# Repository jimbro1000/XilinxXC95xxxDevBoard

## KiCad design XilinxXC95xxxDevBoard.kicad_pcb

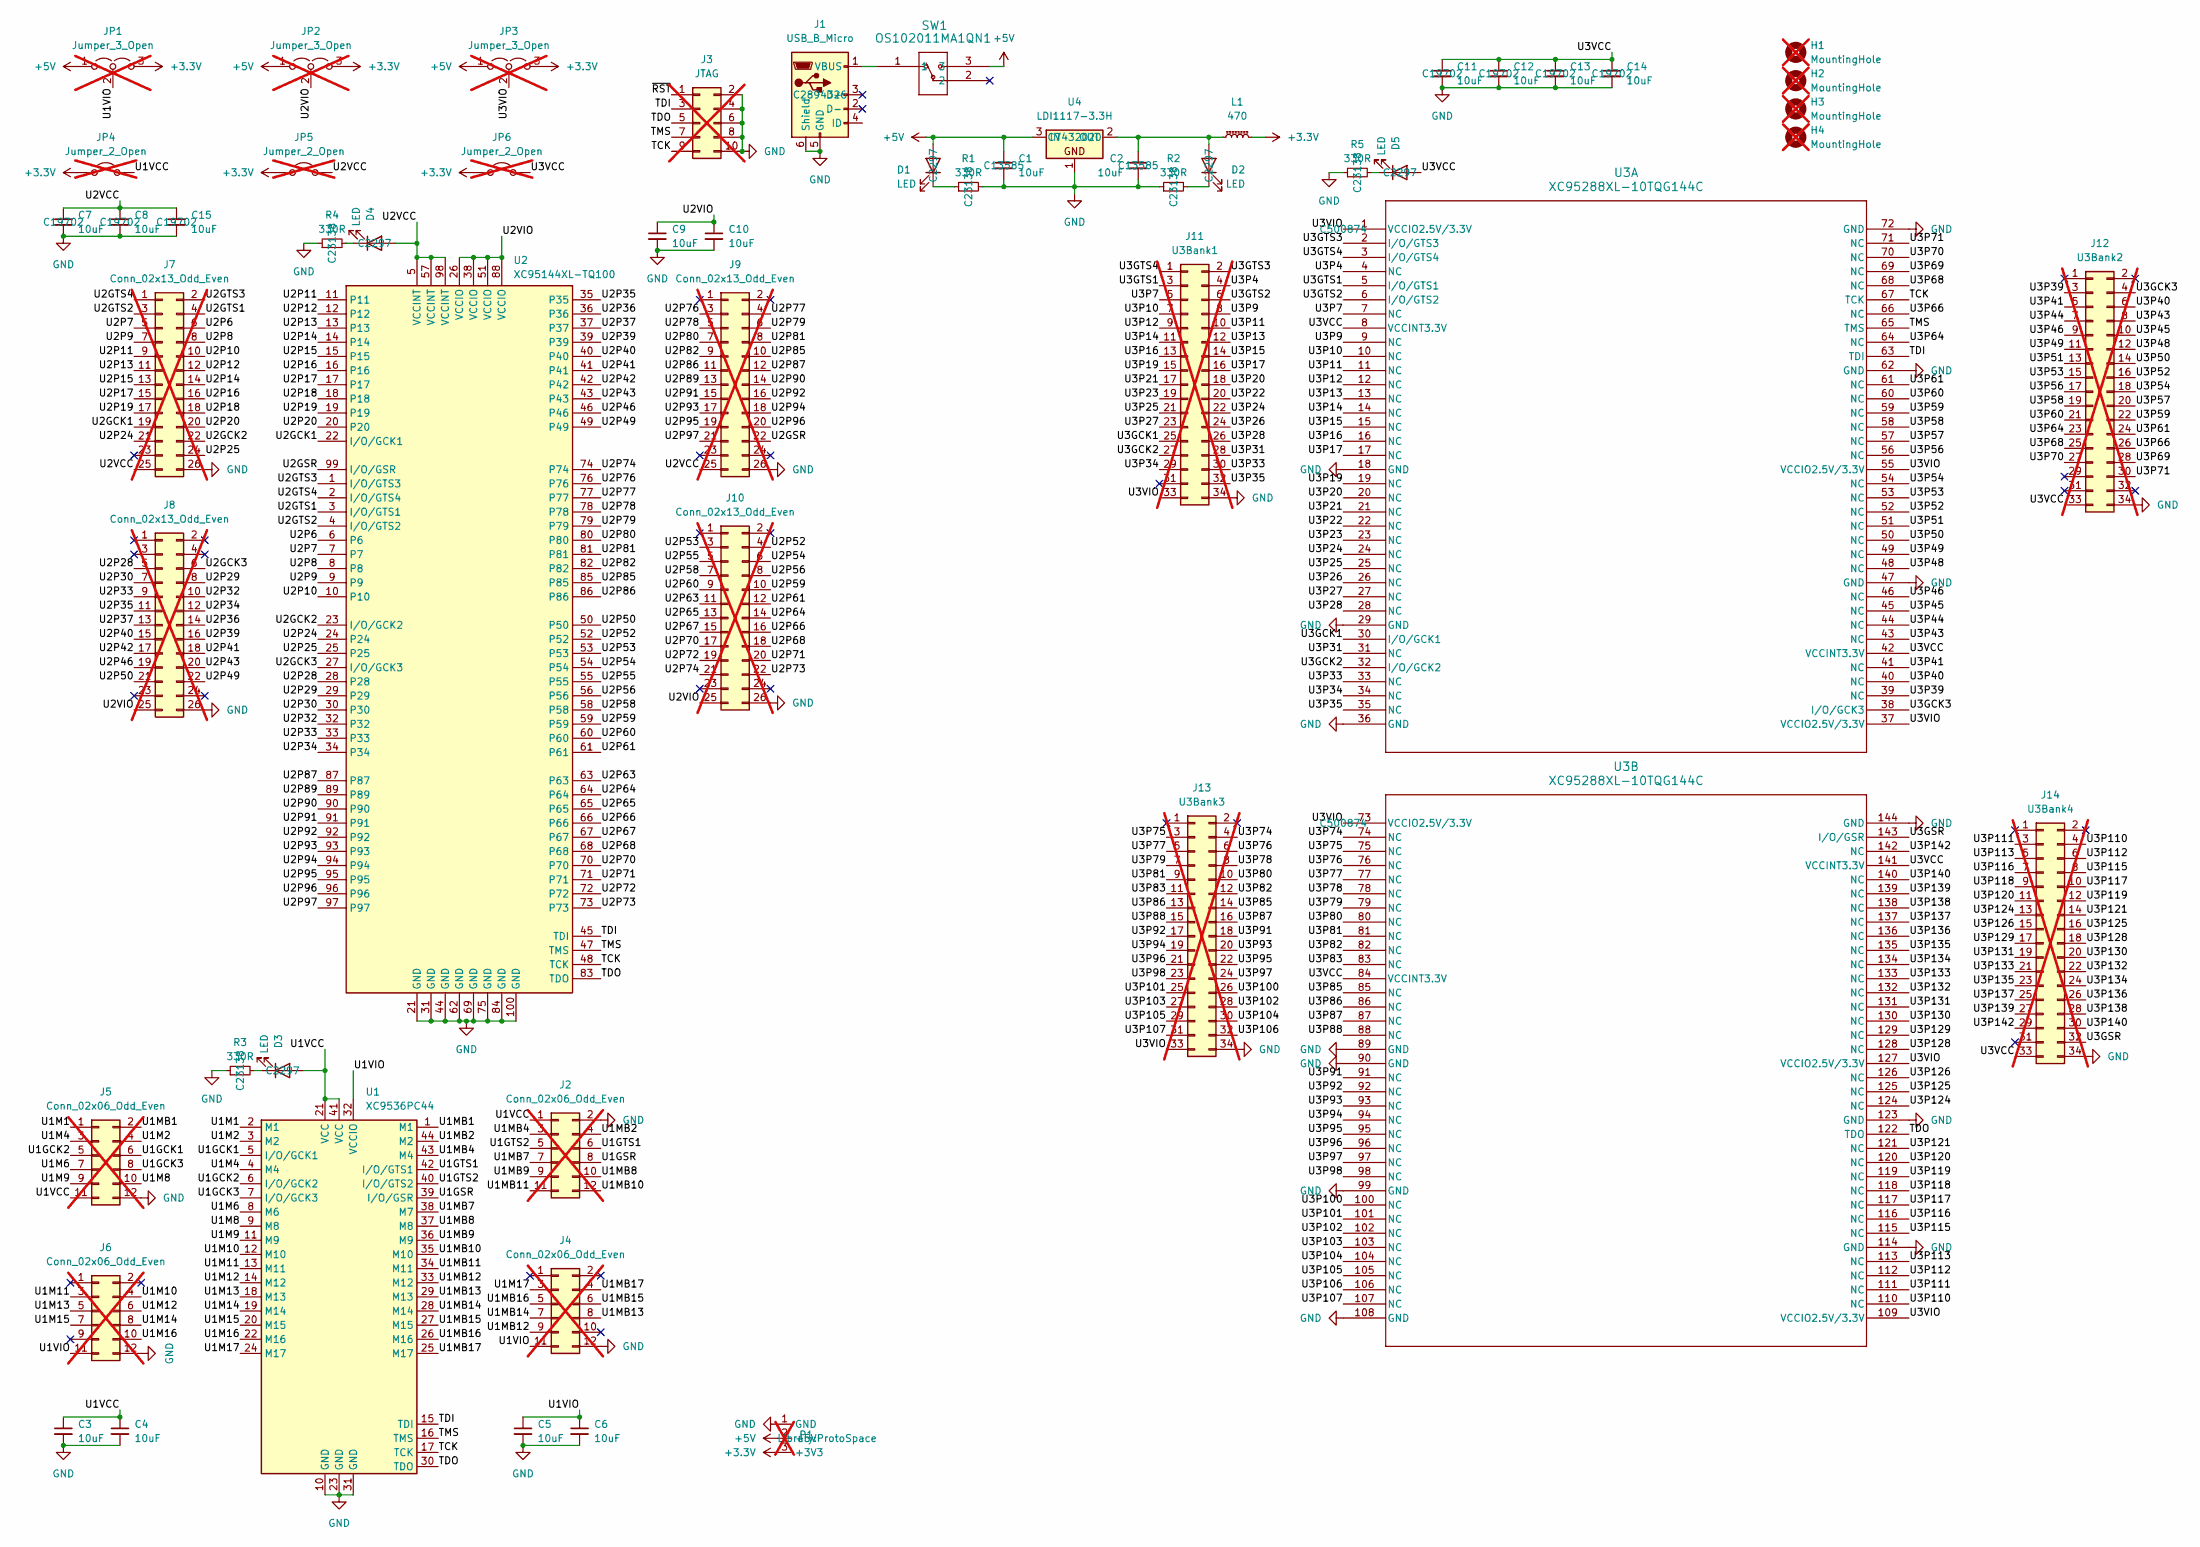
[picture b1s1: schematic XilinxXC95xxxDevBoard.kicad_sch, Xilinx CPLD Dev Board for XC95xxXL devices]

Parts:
C1, C2: 10uF; C_1206_3216Metric; LCSC C13585
C3, C4, C5, C6, C9, C10: 10uF; C_Disc_D3.0mm_W1.6mm_P2.50mm
C7, C8, C11, C12, C13, C14, C15: 10uF; C_0603_1608Metric; LCSC C19702
D1, D2, D3, D4, D5: LED; LED_0805_2012Metric; LCSC C2297
H1, H2, H3, H4: MountingHole; MountingHole_3.2mm_M3_DIN965; not fitted
J1: USB_B_Micro; USB_Micro-B_Wuerth_629105150521; LCSC C2894326
J2, J4, J5, J6: Conn_02x06_Odd_Even; PinHeader_2x06_P2.54mm_Vertical; not fitted
J3: JTAG; IDC-Header_2x05_P2.54mm_Vertical; not fitted
J7, J8, J9, J10: Conn_02x13_Odd_Even; PinHeader_2x13_P2.54mm_Vertical; not fitted
J11: U3Bank1; PinHeader_2x17_P2.54mm_Vertical; not fitted
J12: U3Bank2; PinHeader_2x17_P2.54mm_Vertical; not fitted
J13: U3Bank3; PinHeader_2x17_P2.54mm_Vertical; not fitted
J14: U3Bank4; PinHeader_2x17_P2.54mm_Vertical; not fitted
JP1, JP2, JP3: Jumper_3_Open; PinHeader_1x03_P2.54mm_Vertical; not fitted
JP4, JP5, JP6: Jumper_2_Open; PinHeader_1x02_P2.54mm_Vertical; not fitted
L1: 470; L_10.4x10.4_H4.8; LCSC C7431106
P1: ProtoSpace; not fitted
R1, R2, R3, R4, R5: 330R; R_0603_1608Metric; LCSC C23138
SW1: OS102011MA1QN1; OS102011MA1QN1_CNK; DigiKey CKN9559-ND
U1: XC9536PC44; LQFP-44_10x10mm_P0.8mm
U2: XC95144XL-TQ100; TQFP-100_14x14mm_P0.5mm
U3: XC95288XL-10TQG144C; 144-TQFP_XIL; LCSC C500874
U4: LDI1117-3.3H; SOT-223-3_TabPin2; LCSC C7432020

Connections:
+3.3V: JP1.3 (B), JP2.3 (B), JP3.3 (B), JP4.1 (A), JP5.1 (A), JP6.1 (A), L1.2, P1.3 (+3V3)
+5V: C1.1, D1.2 (A), JP1.1 (A), JP2.1 (A), JP3.1 (A), P1.2 (+5V), SW1.3, U4.3 (IN)
/TCK: J3.9, U1.17 (TCK), U2.48 (TCK), U3.67 (TCK)
/TDI: J3.3, U1.15 (TDI), U2.45 (TDI), U3.63 (TDI)
/TDO: J3.5, U1.30 (TDO), U2.83 (TDO), U3.122 (TDO)
/TMS: J3.7, U1.16 (TMS), U2.47 (TMS), U3.65 (TMS)
/U1GCK1: J5.6, U1.5 (I/O/GCK1)
/U1GCK2: J5.5, U1.6 (I/O/GCK2)
/U1GCK3: J5.8, U1.7 (I/O/GCK3)
/U1GSR: J2.8, U1.39 (I/O/GSR)
/U1GTS1: J2.6, U1.42 (I/O/GTS1)
/U1GTS2: J2.5, U1.40 (I/O/GTS2)
/U1M1: J5.1, U1.2 (M1)
/U1M2: J5.4, U1.3 (M2)
/U1M4: J5.3, U1.4 (M4)
/U1M6: J5.7, U1.8 (M6)
/U1M8: J5.10, U1.9 (M8)
/U1M9: J5.9, U1.11 (M9)
/U1M10: J6.4, U1.12 (M10)
/U1M11: J6.3, U1.13 (M11)
/U1M12: J6.6, U1.14 (M12)
/U1M13: J6.5, U1.18 (M13)
/U1M14: J6.8, U1.19 (M14)
/U1M15: J6.7, U1.20 (M15)
/U1M16: J6.10, U1.22 (M16)
/U1M17: J4.3, U1.24 (M17)
/U1MB1: J5.2, U1.1 (M1)
/U1MB2: J2.4, U1.44 (M2)
/U1MB4: J2.3, U1.43 (M4)
/U1MB7: J2.7, U1.38 (M7)
/U1MB8: J2.10, U1.37 (M8)
/U1MB9: J2.9, U1.36 (M9)
/U1MB10: J2.12, U1.35 (M10)
/U1MB11: J2.11, U1.34 (M11)
/U1MB12: J4.9, U1.33 (M12)
/U1MB13: J4.8, U1.29 (M13)
/U1MB14: J4.7, U1.28 (M14)
/U1MB15: J4.6, U1.27 (M15)
/U1MB16: J4.5, U1.26 (M16)
/U1MB17: J4.4, U1.25 (M17)
/U1VCC: C3.1, C4.1, D3.2 (A), J2.1, J5.11, JP4.2 (B), U1.21 (VCC), U1.41 (VCC)
/U1VIO: C5.1, C6.1, J4.11, J6.11, JP1.2 (C), U1.32 (VCCIO)
/U2GCK1: J7.19, U2.22 (I/O/GCK1)
/U2GCK2: J7.22, U2.23 (I/O/GCK2)
/U2GCK3: J8.6, U2.27 (I/O/GCK3)
/U2GSR: J9.22, U2.99 (I/O/GSR)
/U2GTS1: J7.4, U2.3 (I/O/GTS1)
/U2GTS2: J7.3, U2.4 (I/O/GTS2)
/U2GTS3: J7.2, U2.1 (I/O/GTS3)
/U2GTS4: J7.1, U2.2 (I/O/GTS4)
/U2P6: J7.6, U2.6
/U2P7: J7.5, U2.7
/U2P8: J7.8, U2.8
/U2P9: J7.7, U2.9
/U2P10: J7.10, U2.10
/U2P11: J7.9, U2.11
/U2P12: J7.12, U2.12
/U2P13: J7.11, U2.13
/U2P14: J7.14, U2.14
/U2P15: J7.13, U2.15
/U2P16: J7.16, U2.16
/U2P17: J7.15, U2.17
/U2P18: J7.18, U2.18
/U2P19: J7.17, U2.19
/U2P20: J7.20, U2.20
/U2P24: J7.21, U2.24
/U2P25: J7.24, U2.25
/U2P28: J8.5, U2.28
/U2P29: J8.8, U2.29
/U2P30: J8.7, U2.30
/U2P32: J8.10, U2.32
/U2P33: J8.9, U2.33
/U2P34: J8.12, U2.34
/U2P35: J8.11, U2.35
/U2P36: J8.14, U2.36
/U2P37: J8.13, U2.37
/U2P39: J8.16, U2.39
/U2P40: J8.15, U2.40
/U2P41: J8.18, U2.41
/U2P42: J8.17, U2.42
/U2P43: J8.20, U2.43
/U2P46: J8.19, U2.46
/U2P49: J8.22, U2.49
/U2P50: J8.21, U2.50
/U2P52: J10.4, U2.52
/U2P53: J10.3, U2.53
/U2P54: J10.6, U2.54
/U2P55: J10.5, U2.55
/U2P56: J10.8, U2.56
/U2P58: J10.7, U2.58
/U2P59: J10.10, U2.59
/U2P60: J10.9, U2.60
/U2P61: J10.12, U2.61
/U2P63: J10.11, U2.63
/U2P64: J10.14, U2.64
/U2P65: J10.13, U2.65
/U2P66: J10.16, U2.66
/U2P67: J10.15, U2.67
/U2P68: J10.18, U2.68
/U2P70: J10.17, U2.70
/U2P71: J10.20, U2.71
/U2P72: J10.19, U2.72
/U2P73: J10.22, U2.73
/U2P74: J10.21, U2.74
/U2P76: J9.3, U2.76
/U2P77: J9.4, U2.77
/U2P78: J9.5, U2.78
/U2P79: J9.6, U2.79
/U2P80: J9.7, U2.80
/U2P81: J9.8, U2.81
/U2P82: J9.9, U2.82
/U2P85: J9.10, U2.85
/U2P86: J9.11, U2.86
/U2P87: J9.12, U2.87
/U2P89: J9.13, U2.89
/U2P90: J9.14, U2.90
/U2P91: J9.15, U2.91
/U2P92: J9.16, U2.92
/U2P93: J9.17, U2.93
/U2P94: J9.18, U2.94
/U2P95: J9.19, U2.95
/U2P96: J9.20, U2.96
/U2P97: J9.21, U2.97
/U2VCC: C7.1, C8.1, C15.1, D4.2 (A), J7.25, J9.25, JP5.2 (B), U2.5 (VCCINT), U2.57 (VCCINT), U2.98 (VCCINT)
/U2VIO: C9.1, C10.1, J8.25, J10.25, JP2.2 (C), U2.26 (VCCIO), U2.38 (VCCIO), U2.51 (VCCIO), U2.88 (VCCIO)
/U3GCK1: J11.25, U3.30 (I/O/GCK1)
/U3GCK2: J11.27, U3.32 (I/O/GCK2)
/U3GCK3: J12.4, U3.38 (I/O/GCK3)
/U3GSR: J14.32, U3.143 (I/O/GSR)
/U3GTS1: J11.3, U3.5 (I/O/GTS1)
/U3GTS2: J11.6, U3.6 (I/O/GTS2)
/U3GTS3: J11.2, U3.2 (I/O/GTS3)
/U3GTS4: J11.1, U3.3 (I/O/GTS4)
/U3P4: J11.4, U3.4 (NC)
/U3P7: J11.5, U3.7 (NC)
/U3P9: J11.8, U3.9 (NC)
/U3P10: J11.7, U3.10 (NC)
/U3P11: J11.10, U3.11 (NC)
/U3P12: J11.9, U3.12 (NC)
/U3P13: J11.12, U3.13 (NC)
/U3P14: J11.11, U3.14 (NC)
/U3P15: J11.14, U3.15 (NC)
/U3P16: J11.13, U3.16 (NC)
/U3P17: J11.16, U3.17 (NC)
/U3P19: J11.15, U3.19 (NC)
/U3P20: J11.18, U3.20 (NC)
/U3P21: J11.17, U3.21 (NC)
/U3P22: J11.20, U3.22 (NC)
/U3P23: J11.19, U3.23 (NC)
/U3P24: J11.22, U3.24 (NC)
/U3P25: J11.21, U3.25 (NC)
/U3P26: J11.24, U3.26 (NC)
/U3P27: J11.23, U3.27 (NC)
/U3P28: J11.26, U3.28 (NC)
/U3P31: J11.28, U3.31 (NC)
/U3P33: J11.30, U3.33 (NC)
/U3P34: J11.29, U3.34 (NC)
/U3P35: J11.32, U3.35 (NC)
/U3P39: J12.3, U3.39 (NC)
/U3P40: J12.6, U3.40 (NC)
/U3P41: J12.5, U3.41 (NC)
/U3P43: J12.8, U3.43 (NC)
/U3P44: J12.7, U3.44 (NC)
/U3P45: J12.10, U3.45 (NC)
/U3P46: J12.9, U3.46 (NC)
/U3P48: J12.12, U3.48 (NC)
/U3P49: J12.11, U3.49 (NC)
/U3P50: J12.14, U3.50 (NC)
/U3P51: J12.13, U3.51 (NC)
/U3P52: J12.16, U3.52 (NC)
/U3P53: J12.15, U3.53 (NC)
/U3P54: J12.18, U3.54 (NC)
/U3P56: J12.17, U3.56 (NC)
/U3P57: J12.20, U3.57 (NC)
/U3P58: J12.19, U3.58 (NC)
/U3P59: J12.22, U3.59 (NC)
/U3P60: J12.21, U3.60 (NC)
/U3P61: J12.24, U3.61 (NC)
/U3P64: J12.23, U3.64 (NC)
/U3P66: J12.26, U3.66 (NC)
/U3P68: J12.25, U3.68 (NC)
/U3P69: J12.28, U3.69 (NC)
/U3P70: J12.27, U3.70 (NC)
/U3P71: J12.30, U3.71 (NC)
/U3P74: J13.4, U3.74 (NC)
/U3P75: J13.3, U3.75 (NC)
/U3P76: J13.6, U3.76 (NC)
/U3P77: J13.5, U3.77 (NC)
/U3P78: J13.8, U3.78 (NC)
/U3P79: J13.7, U3.79 (NC)
/U3P80: J13.10, U3.80 (NC)
/U3P81: J13.9, U3.81 (NC)
/U3P82: J13.12, U3.82 (NC)
/U3P83: J13.11, U3.83 (NC)
/U3P85: J13.14, U3.85 (NC)
/U3P86: J13.13, U3.86 (NC)
/U3P87: J13.16, U3.87 (NC)
/U3P88: J13.15, U3.88 (NC)
/U3P91: J13.18, U3.91 (NC)
/U3P92: J13.17, U3.92 (NC)
/U3P93: J13.20, U3.93 (NC)
/U3P94: J13.19, U3.94 (NC)
/U3P95: J13.22, U3.95 (NC)
/U3P96: J13.21, U3.96 (NC)
/U3P97: J13.24, U3.97 (NC)
/U3P98: J13.23, U3.98 (NC)
/U3P100: J13.26, U3.100 (NC)
/U3P101: J13.25, U3.101 (NC)
/U3P102: J13.28, U3.102 (NC)
/U3P103: J13.27, U3.103 (NC)
/U3P104: J13.30, U3.104 (NC)
/U3P105: J13.29, U3.105 (NC)
/U3P106: J13.32, U3.106 (NC)
/U3P107: J13.31, U3.107 (NC)
/U3P110: J14.4, U3.110 (NC)
/U3P111: J14.3, U3.111 (NC)
/U3P112: J14.6, U3.112 (NC)
/U3P113: J14.5, U3.113 (NC)
/U3P115: J14.8, U3.115 (NC)
/U3P116: J14.7, U3.116 (NC)
/U3P117: J14.10, U3.117 (NC)
/U3P118: J14.9, U3.118 (NC)
/U3P119: J14.12, U3.119 (NC)
/U3P120: J14.11, U3.120 (NC)
/U3P121: J14.14, U3.121 (NC)
/U3P124: J14.13, U3.124 (NC)
/U3P125: J14.16, U3.125 (NC)
/U3P126: J14.15, U3.126 (NC)
/U3P128: J14.18, U3.128 (NC)
/U3P129: J14.17, U3.129 (NC)
/U3P130: J14.20, U3.130 (NC)
/U3P131: J14.19, U3.131 (NC)
/U3P132: J14.22, U3.132 (NC)
/U3P133: J14.21, U3.133 (NC)
/U3P134: J14.24, U3.134 (NC)
/U3P135: J14.23, U3.135 (NC)
/U3P136: J14.26, U3.136 (NC)
/U3P137: J14.25, U3.137 (NC)
/U3P138: J14.28, U3.138 (NC)
/U3P139: J14.27, U3.139 (NC)
/U3P140: J14.30, U3.140 (NC)
/U3P142: J14.29, U3.142 (NC)
/U3VCC: C11.1, C12.1, C13.1, C14.1, D5.2 (A), J12.33, J14.33, JP6.2 (B), U3.8 (VCCINT3.3V), U3.42 (VCCINT3.3V), U3.84 (VCCINT3.3V), U3.141 (VCCINT3.3V)
/U3VIO: J11.33, J13.33, JP3.2 (C), U3.1 (VCCIO2.5V/3.3V), U3.37 (VCCIO2.5V/3.3V), U3.55 (VCCIO2.5V/3.3V), U3.73 (VCCIO2.5V/3.3V), U3.109 (VCCIO2.5V/3.3V), U3.127 (VCCIO2.5V/3.3V)
/~RST: J3.1
GND: C1.2, C2.2, C3.2, C4.2, C5.2, C6.2, C7.2, C8.2, C9.2, C10.2, C11.2, C12.2, C13.2, C14.2, C15.2, J1.5 (GND), J1.6 (Shield), J2.2, J3.2, J3.4, J3.6, J3.8, J3.10, J4.12, J5.12, J6.12, J7.26, J8.26, J9.26, J10.26, J11.34, J12.34, J13.34, J14.34, P1.1 (GND), R1.2, R2.1, R3.1, R4.1, R5.1, U1.10 (GND), U1.23 (GND), U1.31 (GND), U2.21 (GND), U2.31 (GND), U2.44 (GND), U2.62 (GND), U2.69 (GND), U2.75 (GND), U2.84 (GND), U2.100 (GND), U3.18 (GND), U3.29 (GND), U3.36 (GND), U3.47 (GND), U3.62 (GND), U3.72 (GND), U3.89 (GND), U3.90 (GND), U3.99 (GND), U3.108 (GND), U3.114 (GND), U3.123 (GND), U3.144 (GND), U4.1
unnamed: D1.1 (K), R1.1
unnamed: C2.1, D2.2 (A), L1.1, U4.2 (OUT)
unnamed: D2.1 (K), R2.2
unnamed: D3.1 (K), R3.2
unnamed: D4.1 (K), R4.2
unnamed: D5.1 (K), R5.2
unnamed: J1.1 (VBUS), SW1.1

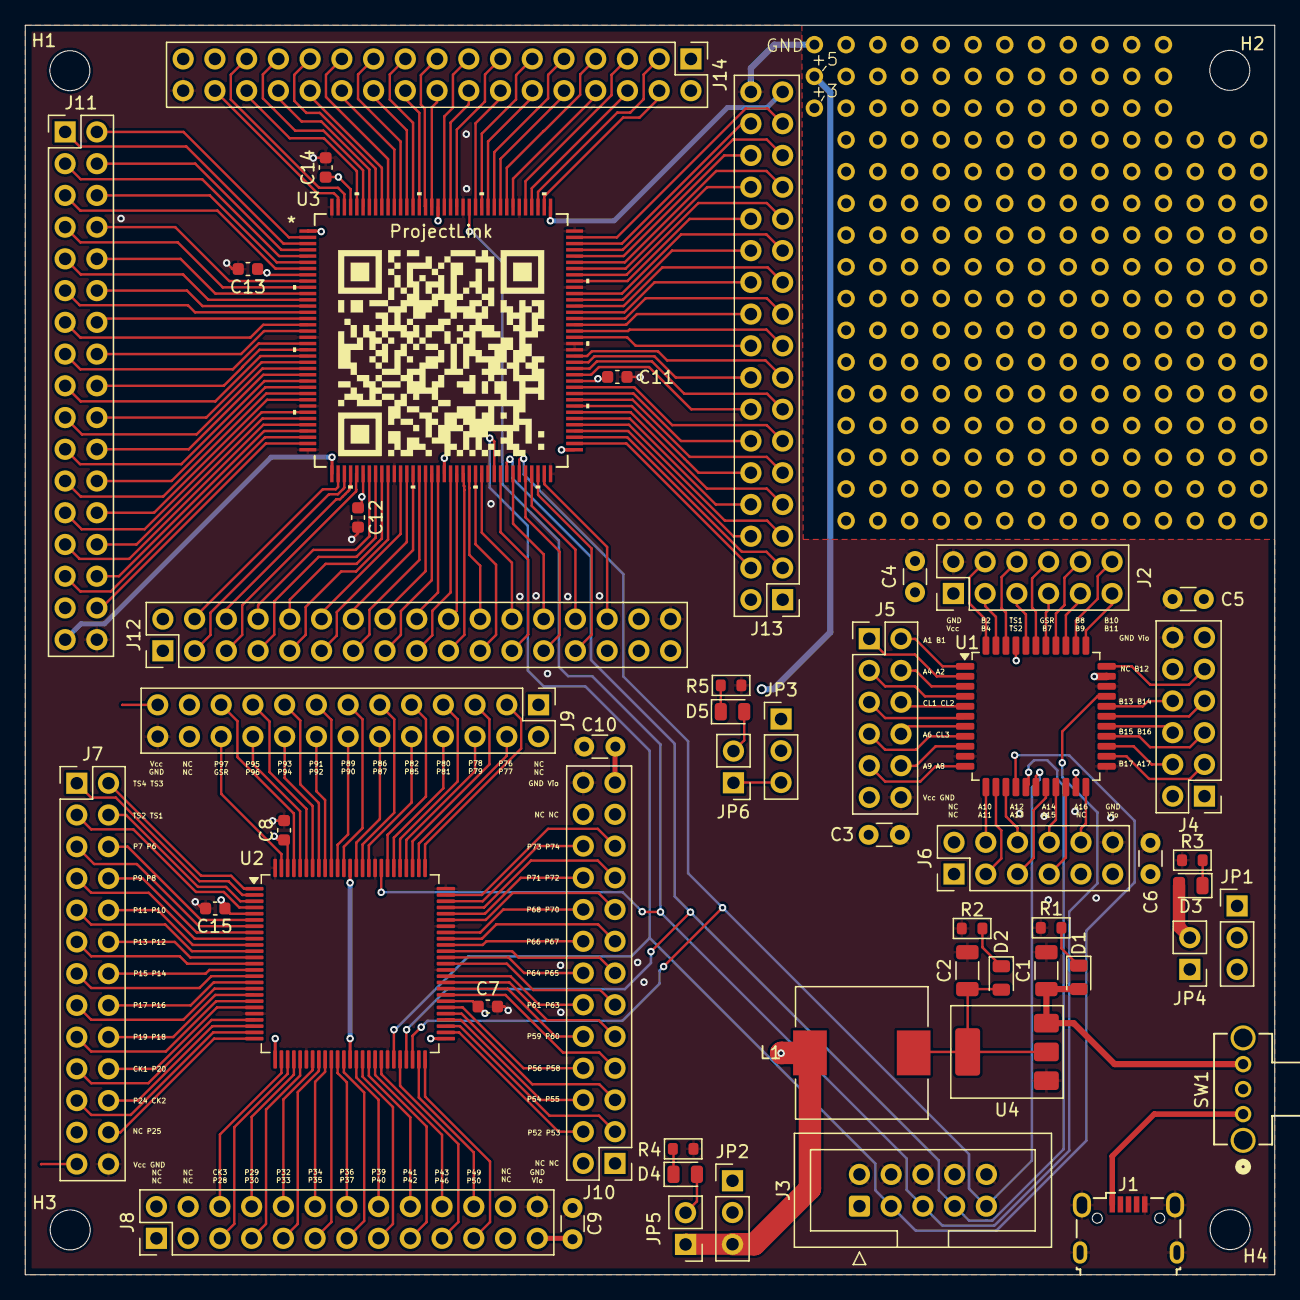
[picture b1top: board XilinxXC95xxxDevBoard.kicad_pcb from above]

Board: 4 copper layers, 100.0 x 100.0 mm, 58 parts (1 on the bottom side), 252 nets.

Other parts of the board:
QR*****: ProjectLink
QR*****#2: https://github.com/jimbro1000/XilinxXC95xxxDevBoa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; ProjectLink

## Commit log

2025-06-14 refine labelling
